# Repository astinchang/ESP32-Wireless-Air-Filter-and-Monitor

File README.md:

# ESP32 Air Filter and Monitor

## **Project Report**

### **Project Overview**

This project is an automatic air filtration system built around an ESP32 microcontroller. The goal of the project is to improve indoor air quality while saving energy by only increasing fan speed when the air quality gets worse. The system uses a particulate matter sensor to measure the amount of particles in the air, a temperature and humidity sensor to monitor environmental conditions, PWM-controlled fans to move air through filters, a MicroSD card module to log air quality data over time, and WiFi tracking so that air quality trends could be monitored from a phone or laptop.

The basic idea is that the ESP32 reads sensor data, decides how dirty the air is, and adjusts the speed of the fans accordingly. If the particulate matter level is low, the fans can run at a lower speed to save power. If the particulate matter level rises, the fans ramp up to clean the air more quickly. This makes the system more efficient than having the fans run constantly. I also included a push button that can interrupt the system to force the fans off, for safety.

### **Components and Their Purpose**

- The main MCU for the project is the ESP32C6-DevKitC-1. It implements the basic features I need to get this project running: I2C, SPI, and UART communication, with WiFi and PWM capabilities. The ESP32 is also low power.
- The PMS5003 particulate matter sensor measures the amount of particulate matter in the air. This component is polled to check air quality at the PM2.5 (particles <2.5um diameter) level, although it does estimate other particle sizes, useful for data reporting. We use this sensor to control the fans' PWM level.
- The HDC3022 temperature and humidity sensor measures the surrounding temperature and humidity. This sensor really helps the node be a more complete source of information, because air quality readings can be affected by humidity. Also useful for more complete, environmental monitoring.
- The PWM PC fans are used to pull air through the filter. They are controlled using PWM output from the ESP32. This is necessary for saving energy and making the air filter respond gradually to different air quality levels.
- The air filters physically remove particles from the air as the fans pull air through the system. These are the part of the project that actually performs the cleaning.
- The MicroSD card module is used for non-volatile data logging. This allows the system to save particulate matter, temperature, and humidity data over time. The MicroSD module is important because it lets the user look back at how air quality changed instead of only seeing the current reading.
- The foam board was used as the physical body of the air filter. It held the fans, filters, sensors, and wiring together. While it worked for a prototype, it was not as sturdy or polished as a real product enclosure.

CREDIT TO JOEY FOX FOR THE AIR FILTER DESIGN: https://itsairborne.com/building-a-pc-fan-corsi-rosenthal-box-68e7cd1ca570 

### **Problems Encountered**

One of the biggest issues was the physical wiring and construction. Since the project was built as a prototype, wiring parts from the wall and connecting everything cleanly was more difficult than expected. The system had several separate parts that needed power, especially with needing to split the 12V power from the wall adapter 3 ways: the 2 sets of fans and buck converter to the breadboard (I split the 6 fans into 2 sets because I didn't feel comfortable daisy chaining 6 together). I also realized midway that using the flimsy breadboard wire was probably not safe and causing overheating, so buying new wire and using wire nuts was necessary, although it made keeping the wiring organized a challenge.

Another issue was that the project was built using a breadboard and foam board instead of a custom PCB and enclosure. This made the system easier to prototype and change, but it also made it more fragile and less clean-looking. Wires were mostly loose, connections were less secure, and the final build was not as sturdy as a real embedded product.

### **Comparison to Real-World Embedded Systems**

This project is similar to real-world embedded systems because it uses sensors, a microcontroller, actuator control, data logging, and low-power design ideas. Like many real embedded systems, it reads information from the environment, processes that data, and controls hardware based on the result. It also uses common embedded communication methods such as serial communication, I2C, SPI, PWM, and WiFi.

The project is different from a real-world embedded system in its physical construction. A commercial air quality monitor or smart air purifier would likely use a mounted PCB, proper connectors, a stronger enclosure, and more fixed wiring. Real products also usually go through more testing for safety, durability, airflow efficiency, and long-term reliability. In comparison, this project was more of a functional prototype built with available class materials, breadboard wiring, and foam board.

### **Future Improvements**

With more time and resources, the biggest improvement would be moving the circuit off the breadboard and onto a custom PCB. This would make the system much more reliable, compact, and easier to mount inside an enclosure. Another improvement would be using 3D printing to create a better electrical box and outer enclosure. A 3D-printed enclosure would protect the electronics, organize the wiring, and make the project look closer to a real consumer product.

Overall, this project successfully implements an ESP32-controlled smart air filter. It senses air quality, adjusts fan speed, and logs environmental data, while also showing how embedded systems can be used to make everyday devices more customizable and energy efficient.

## **Wiring Diagrams**

<br>
The diagram above shows how the system is powered from the wall outlet. As I said before, I separated the PC fans into 2 sets of 3 daisy chained together, because I didn't want to daisy chain all of them together. Starting from the wall outlet, I used an AC to DC plug and barrel jack to two terminal connector to separate the voltage and ground wire. Afterwards, took voltage wire and split it into 3 wires: two for the aforementioned fans, one leading to 12V to 5V buck converter for the ESP32 input voltage. All grounds in this chain are tied to a universal ground inside of a screw terminal bus bar. The breadboard/ESP32 logic is described in the next diagram:
<br>
<br>

<br>
Diagram above shows the ESP32 pinout I used to connect all peripherals using the ESP32 and 2 breadboards. As for the power, the 3.3V power was supplied by the ESP32, the 5V power was used as the input for the MCU, and all grounds were tied to the screw terminal bus bar. For the peripherals, pins 4-5 are used for UART to the particle sensor, pin 6 is used for PWM to control the fan speed, pin 0 is used for digital input (input pullup) for the fan shut off button, pins 22-23 are used for I2C to the temp/humidity sensor, and finally pins 18-21 are used for SPI to the microSD card module. 
<br>
<br>

## Libraries Used
The following libraries/APIs were used:

- Arduino.h: Core Arduino/ESP32 functions such as pinMode, delay, millis, Serial, and basic sketch structure.
- Wire.h: Arduino I2C library used to communicate with the HDC3022 temperature/humidity sensor.
- WiFi.h: ESP32 WiFi library used to create the ESP32 access point and host the web dashboard.
- Adafruit_PM25AQI: Adafruit library used to read data from the PMS5003 particulate matter sensor over UART.
- Adafruit_HDC302x: Adafruit library used to read temperature and humidity from the HDC3022 sensor.
- SPI.h: Arduino SPI library used for communication with the microSD card module.
- SD.h: Arduino SD card library used to create and append data to airlog.csv on the microSD card.

## KiCAD Build
*Implemented hardware designed above in dedicated PCB with slight differences (FIRST SOLO BUILD DON'T JUDGE LOL):
- ESP32-C6-WROOM-1 microcontroller
- USB-C programming through CP2102N
- 5 V to 3.3 V regulation
- I2C, SPI, and UART expansion headers
<br>
IF TRYING TO GET THIS TO WORK FROM MY FILES MAKE SURE TO DOWNLOAD THESE LIBRARIES: <br>
- 10171746-00021LF <br>
- ESD122DMYR <br>
- espressifLibraries <br>

<br>

<br>

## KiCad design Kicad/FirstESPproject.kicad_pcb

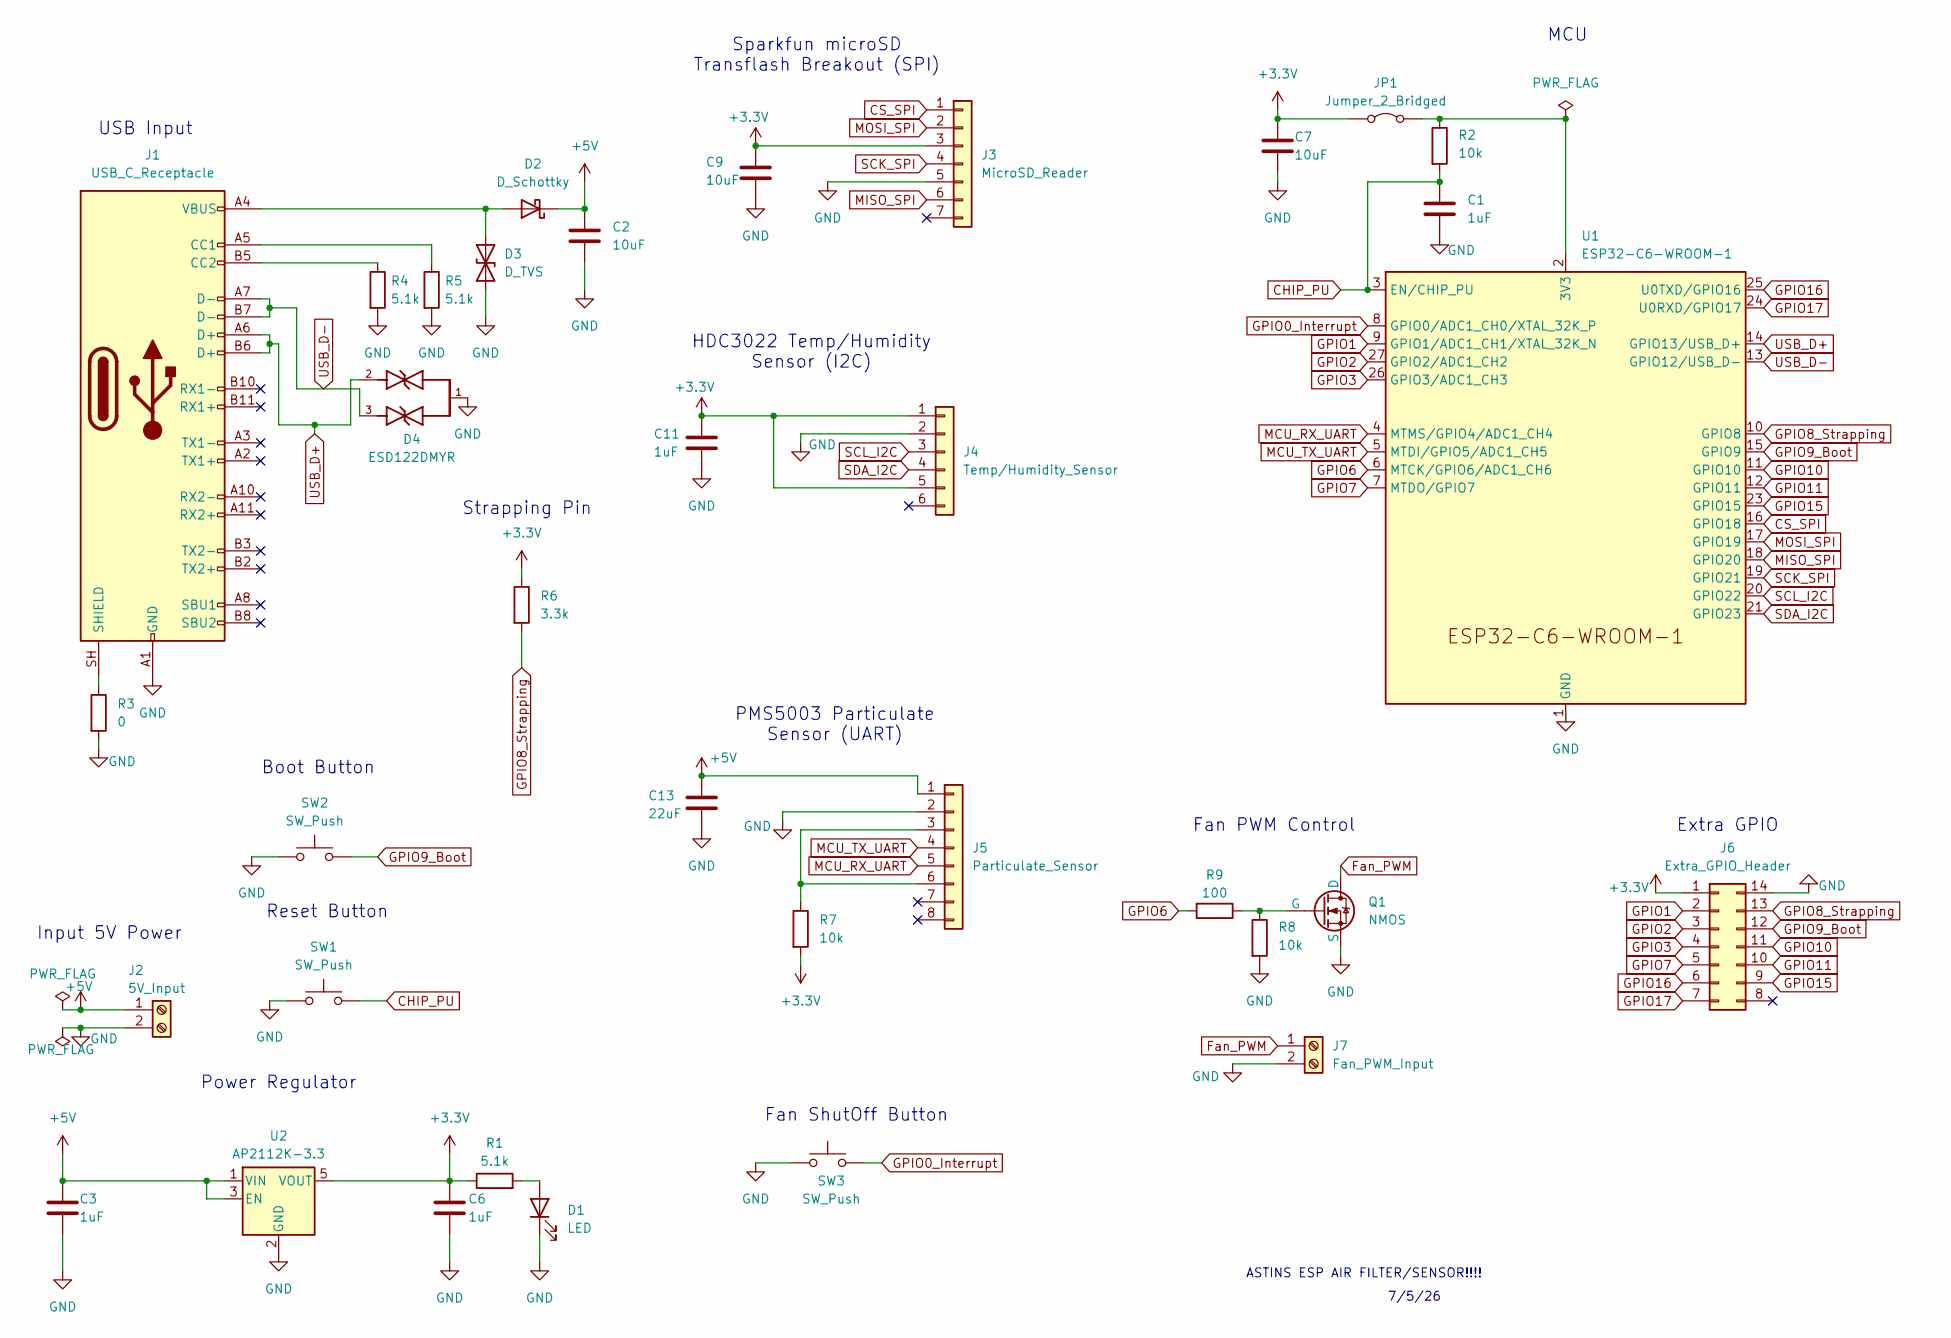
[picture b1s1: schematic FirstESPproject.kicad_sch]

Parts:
C1, C3, C6, C11: 1uF; C_0603_1608Metric; MFG Part Number CC0603ZRY5V7BB105
C2, C7, C9: 10uF; C_0805_2012Metric; MFG Part Number CC0805KRX5R7BB106
C13: 22uF; C_1206_3216Metric; MFG Part Number CC1206MKX5R8BB226
D1: LED; LED_0603_1608Metric; MFG Part Number 150060RS75000
D2: D_Schottky; D_SOD-123; MFG Part Number 1N4148W-TP
D3: D_TVS; D_SOD-123F; MFG Part Number SMF5-0A
D4: ESD122DMYR; DIO_ESD122DMYR; PARTREV A
J1: USB_C_Receptacle; USB_C_Receptacle_Amphenol_12401610E4-2A; MFG Part Number 12401610E4#2A
J2: 5V_Input; TerminalBlock_MaiXu_MX126-5.0-02P_1x02_P5.00mm; MFG Part Number MX126R-5.0-02P-GN01-Cu-S-A
J3: MicroSD_Reader; PinSocket_1x07_P2.54mm_Vertical; MFG Part Number 929974-01-07-RK
J4: Temp/Humidity_Sensor; PinSocket_1x06_P2.54mm_Vertical; MFG Part Number 61300611821
J5: Particulate_Sensor; PinSocket_1x08_P2.54mm_Vertical; MFG Part Number 61300811821
J6: Extra_GPIO_Header; PinSocket_2x07_P2.54mm_Vertical; MFG Part Number 61301421821
J7: Fan_PWM_Input; TerminalBlock_MaiXu_MX126-5.0-02P_1x02_P5.00mm; MFG Part Number MX126R-5.0-02P-GN01-Cu-S-A
JP1: Jumper_2_Bridged; SolderJumper-2_P1.3mm_Bridged_RoundedPad1.0x1.5mm
Q1: NMOS; SOT-23; MFG Part Number BVSS138LT1G
R1, R4, R5: 5.1k; R_0603_1608Metric; MFG Part Number RC0603FR-075K1L
R2, R7, R8: 10k; R_0603_1608Metric; MFG Part Number RC0603JR-0710KL
R3: 0; R_0603_1608Metric; MFG Part Number RC0603JR-070RL
R6: 3.3k; R_0603_1608Metric; MFG Part Number RC0603FR-073K3L
R9: 100; R_0603_1608Metric; MFG Part Number RMCA0603JT100R-HP
SW1, SW2, SW3: SW_Push; SW_PUSH_6mm; MFG Part Number TL1105AF160Q
U1: ESP32-C6-WROOM-1; MFG Part Number ESP32-C6-WROOM-1-N8
U2: AP2112K-3.3; SOT-23-5; MFG Part Number AP2112K-3.3TRG1

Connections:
+3.3V: C6.1, C7.1, C9.1, C11.1, J3.3, J4.1, J4.5, J6.1, JP1.1 (A), R1.1, R6.1, R7.2, U2.5 (VOUT)
+5V: C2.1, C3.1, C13.1, D2.1 (K), J2.1, J5.1, U2.1 (VIN), U2.3 (EN)
CHIP_PU: C1.1, R2.2, SW1.2, U1.3 (EN/CHIP_PU)
CS_SPI: J3.1, U1.16 (GPIO18)
Fan_PWM: J7.1, Q1.1 (D)
GND: C1.2, C2.2, C3.2, C6.2, C7.2, C9.2, C11.2, C13.2, D1.1 (K), D3.1 (A1), D4.1, J1.A1 (GND), J1.A12 (GND), J1.B1 (GND), J1.B12 (GND), J2.2, J3.5, J4.2, J5.2, J6.14, J7.2, Q1.3 (S), R3.2, R4.2, R5.2, R8.2, SW1.1, SW2.1, SW3.1, U1.1 (GND), U1.28 (GND), U1.29 (GND), U2.2 (GND)
GPIO0_Interrupt: SW3.2, U1.8 (GPIO0/ADC1_CH0/XTAL_32K_P)
GPIO1: J6.2, U1.9 (GPIO1/ADC1_CH1/XTAL_32K_N)
GPIO2: J6.3, U1.27 (GPIO2/ADC1_CH2)
GPIO3: J6.4, U1.26 (GPIO3/ADC1_CH3)
GPIO6: R9.2, U1.6 (MTCK/GPIO6/ADC1_CH6)
GPIO7: J6.5, U1.7 (MTDO/GPIO7)
GPIO8_Strapping: J6.13, R6.2, U1.10 (GPIO8)
GPIO9_Boot: J6.12, SW2.2, U1.15 (GPIO9)
GPIO10: J6.11, U1.11 (GPIO10)
GPIO11: J6.10, U1.12 (GPIO11)
GPIO15: J6.9, U1.23 (GPIO15)
GPIO16: J6.6, U1.25 (U0TXD/GPIO16)
GPIO17: J6.7, U1.24 (U0RXD/GPIO17)
MCU_RX_UART: J5.5, U1.4 (MTMS/GPIO4/ADC1_CH4)
MCU_TX_UART: J5.4, U1.5 (MTDI/GPIO5/ADC1_CH5)
MISO_SPI: J3.6, U1.18 (GPIO20)
MOSI_SPI: J3.2, U1.17 (GPIO19)
unnamed: D1.2 (A), R1.2
unnamed: D2.2 (A), D3.2 (A2), J1.A4 (VBUS), J1.A9 (VBUS), J1.B4 (VBUS), J1.B9 (VBUS)
unnamed: J1.A5 (CC1), R5.1
unnamed: J1.B5 (CC2), R4.1
unnamed: J1.SH (SHIELD), R3.1
unnamed: J5.3, J5.6, R7.1
unnamed: JP1.2 (B), R2.1, U1.2 (3V3)
unnamed: Q1.2 (G), R8.1, R9.1
SCK_SPI: J3.4, U1.19 (GPIO21)
SCL_I2C: J4.3, U1.20 (GPIO22)
SDA_I2C: J4.4, U1.21 (GPIO23)
USB_D+: D4.2, J1.A6 (D+), J1.B6 (D+), U1.14 (GPIO13/USB_D+)
USB_D-: D4.3, J1.A7 (D-), J1.B7 (D-), U1.13 (GPIO12/USB_D-)

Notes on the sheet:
Reset Button
PMS5003 Particulate Sensor (UART)
Power Regulator
Boot Button
USB Input
Input 5V Power
Fan ShutOff Button
Sparkfun microSD Transflash Breakout (SPI)
ASTINS ESP AIR FILTER/SENSOR!!!!
7/5/26
Extra GPIO
MCU
Strapping Pin
HDC3022 Temp/Humidity Sensor (I2C)
Fan PWM Control

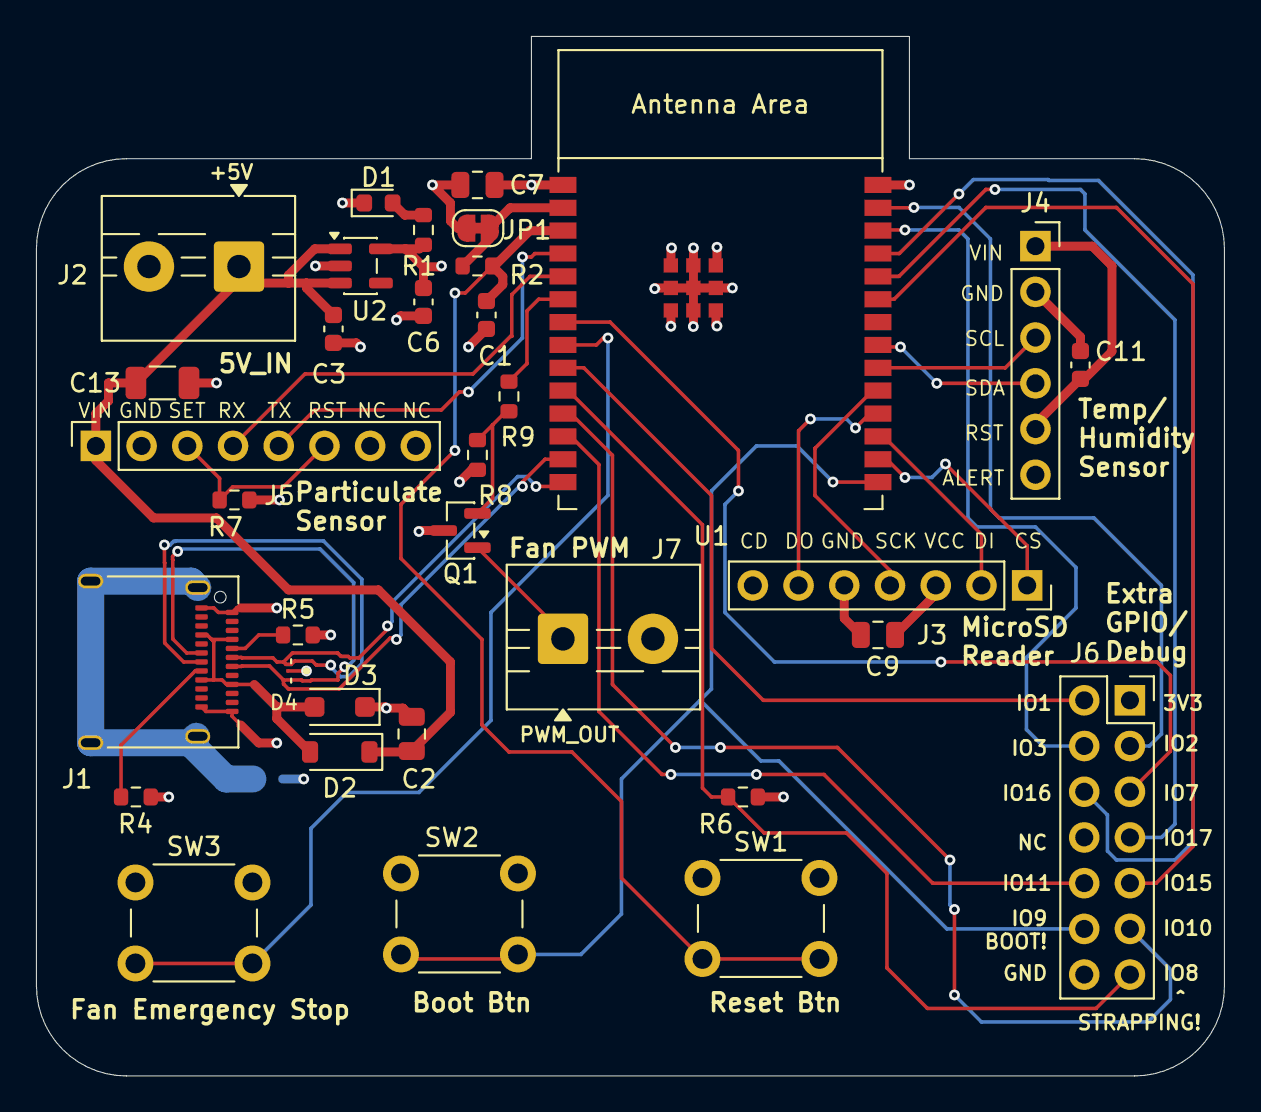
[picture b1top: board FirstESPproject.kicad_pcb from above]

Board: 4 copper layers, 66.0 x 57.8 mm, 35 parts (1 on the bottom side), 36 nets.

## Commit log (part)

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2026-05-18 Rename ESP32AirFilterCode (1).ino to ESP32AirFilterCode.ino
2026-05-18 Rename ESP32AirFilterPic (1).jpg to ESP32AirFilterPic.jpg
